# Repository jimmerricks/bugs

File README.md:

# Bugs

Opinionated ergonomic keyboards.

## Flea v0.1

## Gnat v0.2.1

## Midge v0.3

## Mosquito v0.1.1

## Wasp v0.1.1

## Yellowjacket v0.1.2

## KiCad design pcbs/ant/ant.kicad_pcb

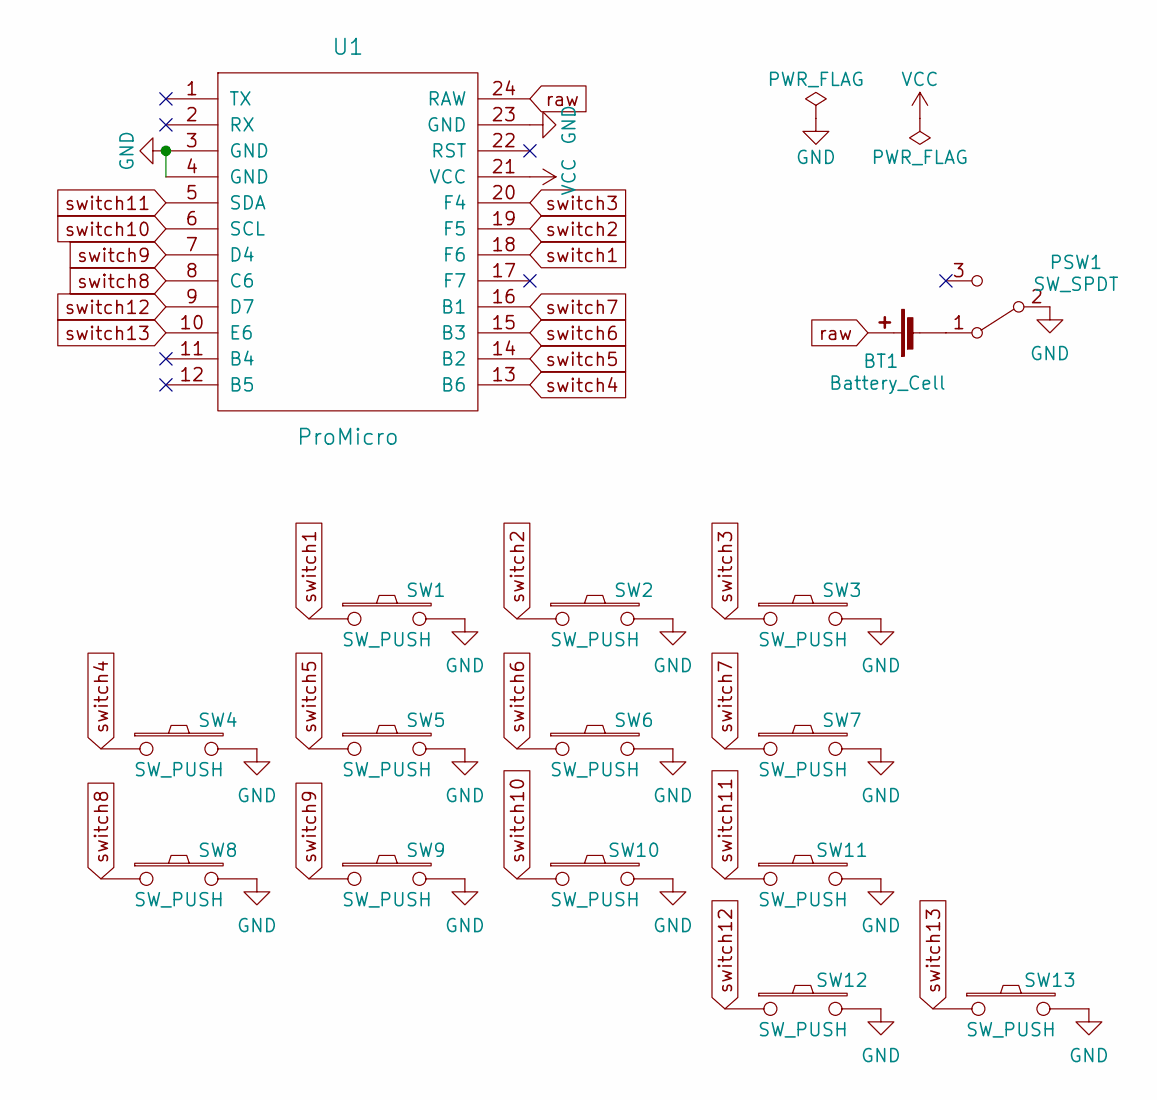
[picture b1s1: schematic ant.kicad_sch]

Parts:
BT1: Battery_Cell; Battery_pads_reversible
PSW1: SW_SPDT; Power_reversible
SW1, SW2, SW3, SW4, SW5, SW6, SW7, SW8, SW9, SW10, SW11, SW12, SW13: SW_PUSH; Choc_reversible
U1: ProMicro; ProMicro_jumpers

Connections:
GND: PSW1.2 (B), SW1.2, SW2.2, SW3.2, SW4.2, SW5.2, SW6.2, SW7.2, SW8.2, SW9.2, SW10.2, SW11.2, SW12.2, SW13.2, U1.3 (GND), U1.4 (GND), U1.23 (GND)
unnamed: BT1.2 (-), PSW1.1 (A)
VCC: U1.21 (VCC)
raw: BT1.1 (+), U1.24 (RAW)
switch1: SW1.1, U1.18 (F6)
switch2: SW2.1, U1.19 (F5)
switch3: SW3.1, U1.20 (F4)
switch4: SW4.1, U1.13 (B6)
switch5: SW5.1, U1.14 (B2)
switch6: SW6.1, U1.15 (B3)
switch7: SW7.1, U1.16 (B1)
switch8: SW8.1, U1.8 (C6)
switch9: SW9.1, U1.7 (D4)
switch10: SW10.1, U1.6 (SCL)
switch11: SW11.1, U1.5 (SDA)
switch12: SW12.1, U1.9 (D7)
switch13: SW13.1, U1.10 (E6)

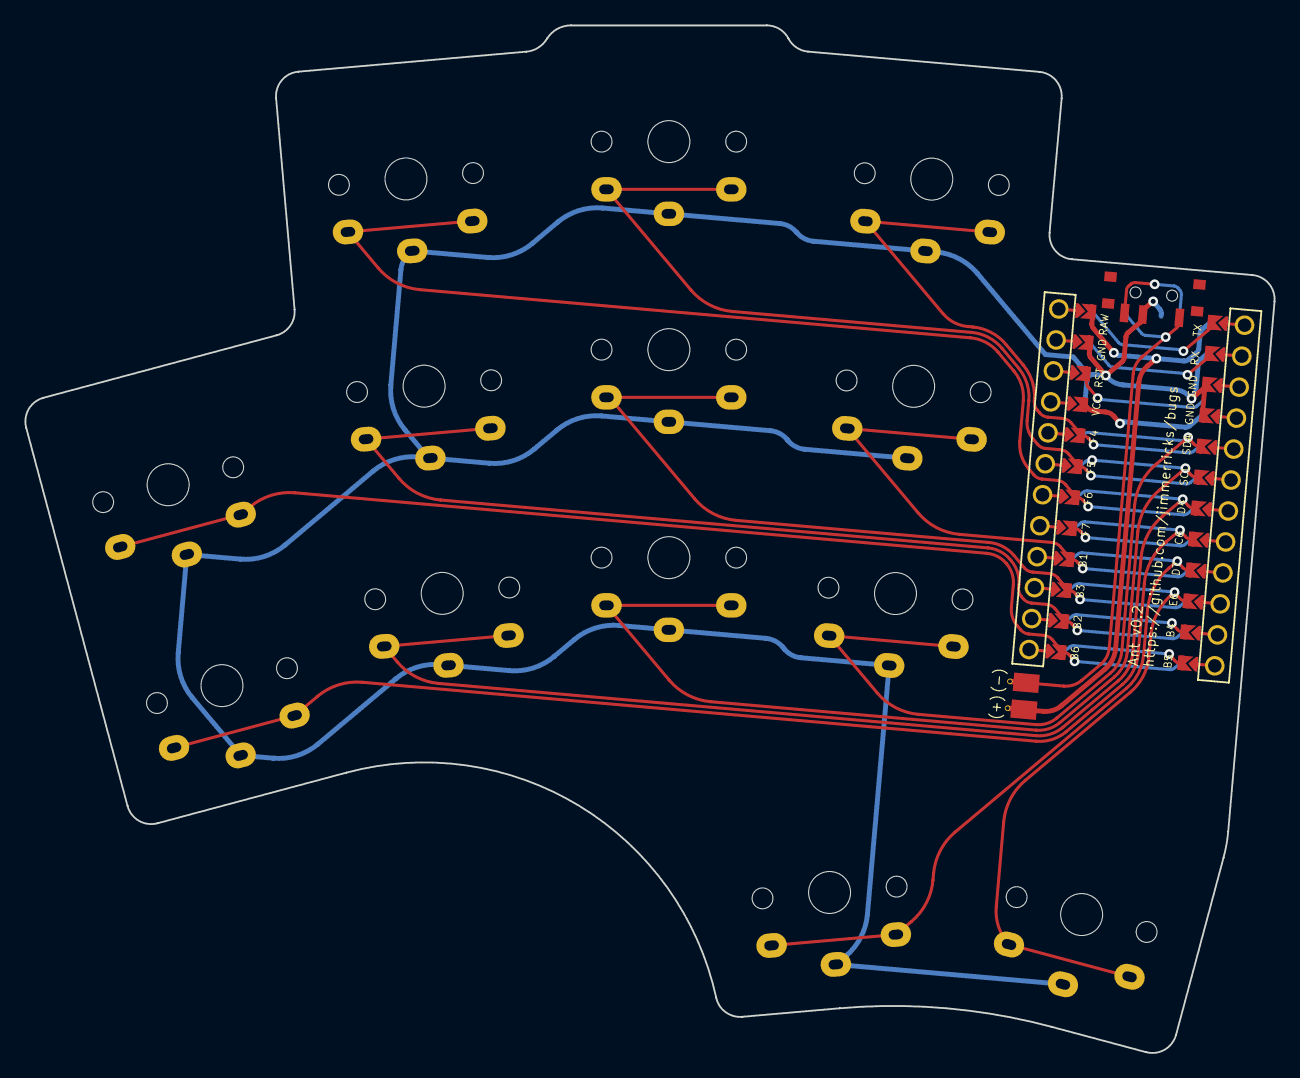
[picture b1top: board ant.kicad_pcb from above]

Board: 2 copper layers, 102.1 x 84.0 mm, 16 parts (0 on the bottom side), 16 nets.

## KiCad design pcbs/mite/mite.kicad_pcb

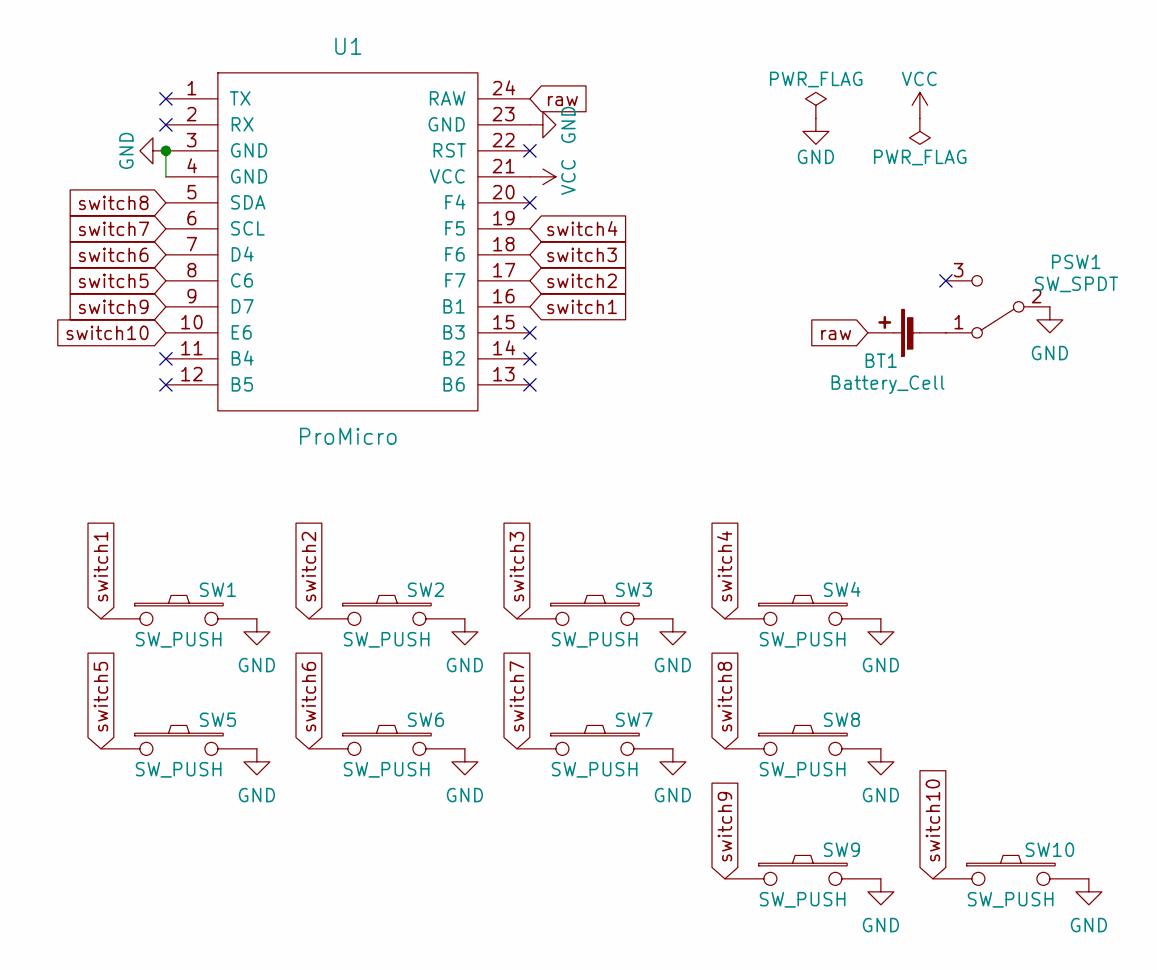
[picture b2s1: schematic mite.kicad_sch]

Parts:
BT1: Battery_Cell; Battery_pads_reversible
PSW1: SW_SPDT; Power_reversible
SW1, SW2, SW3, SW4, SW5, SW6, SW7, SW8, SW9, SW10: SW_PUSH; Choc_reversible
U1: ProMicro; ProMicro_jumpers

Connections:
GND: PSW1.2 (B), SW1.2, SW2.2, SW3.2, SW4.2, SW5.2, SW6.2, SW7.2, SW8.2, SW9.2, SW10.2, U1.3 (GND), U1.4 (GND), U1.23 (GND)
unnamed: BT1.2 (-), PSW1.1 (A)
VCC: U1.21 (VCC)
raw: BT1.1 (+), U1.24 (RAW)
switch1: SW1.1, U1.16 (B1)
switch2: SW2.1, U1.17 (F7)
switch3: SW3.1, U1.18 (F6)
switch4: SW4.1, U1.19 (F5)
switch5: SW5.1, U1.8 (C6)
switch6: SW6.1, U1.7 (D4)
switch7: SW7.1, U1.6 (SCL)
switch8: SW8.1, U1.5 (SDA)
switch9: SW9.1, U1.9 (D7)
switch10: SW10.1, U1.10 (E6)

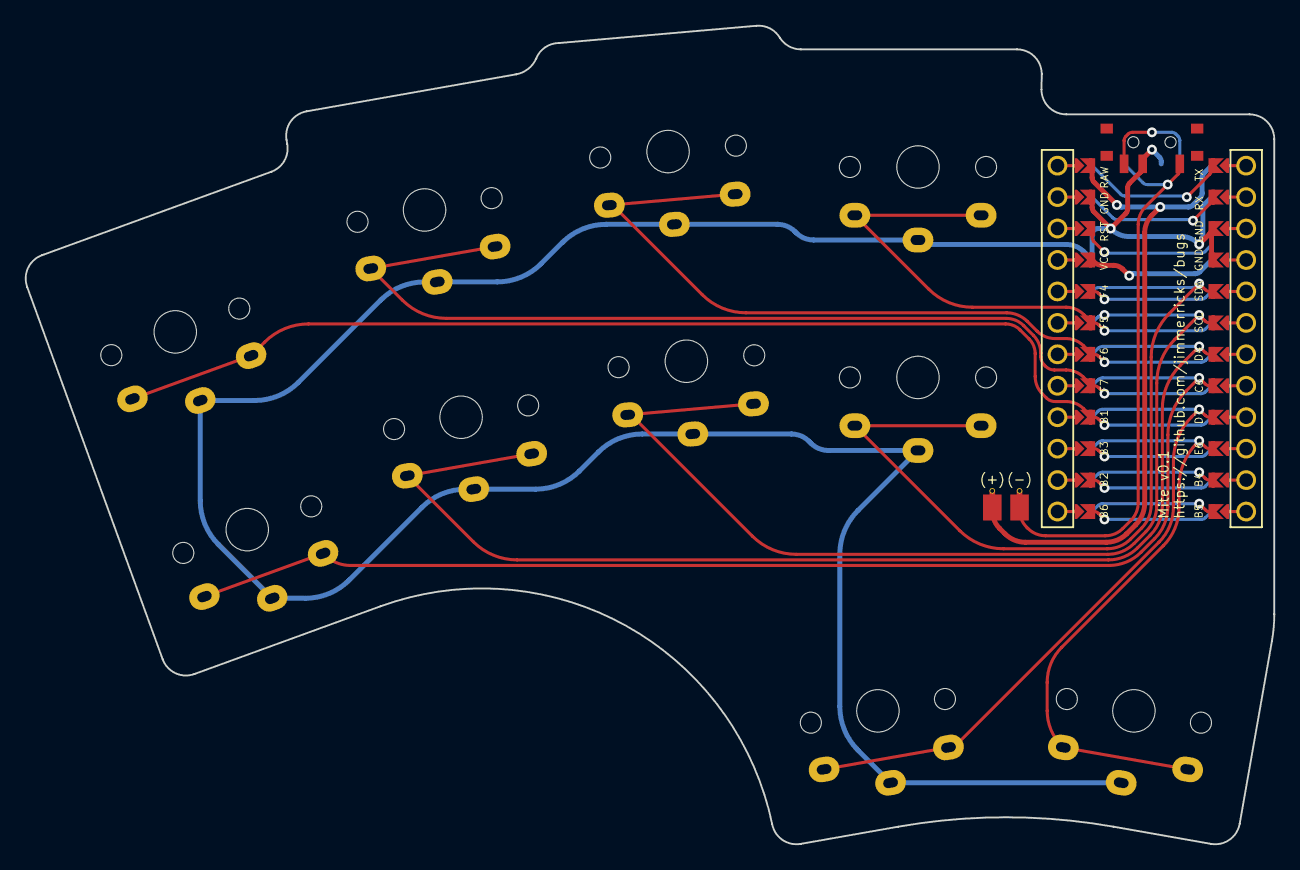
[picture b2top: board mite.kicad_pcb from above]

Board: 2 copper layers, 100.9 x 66.1 mm, 13 parts (0 on the bottom side), 13 nets.

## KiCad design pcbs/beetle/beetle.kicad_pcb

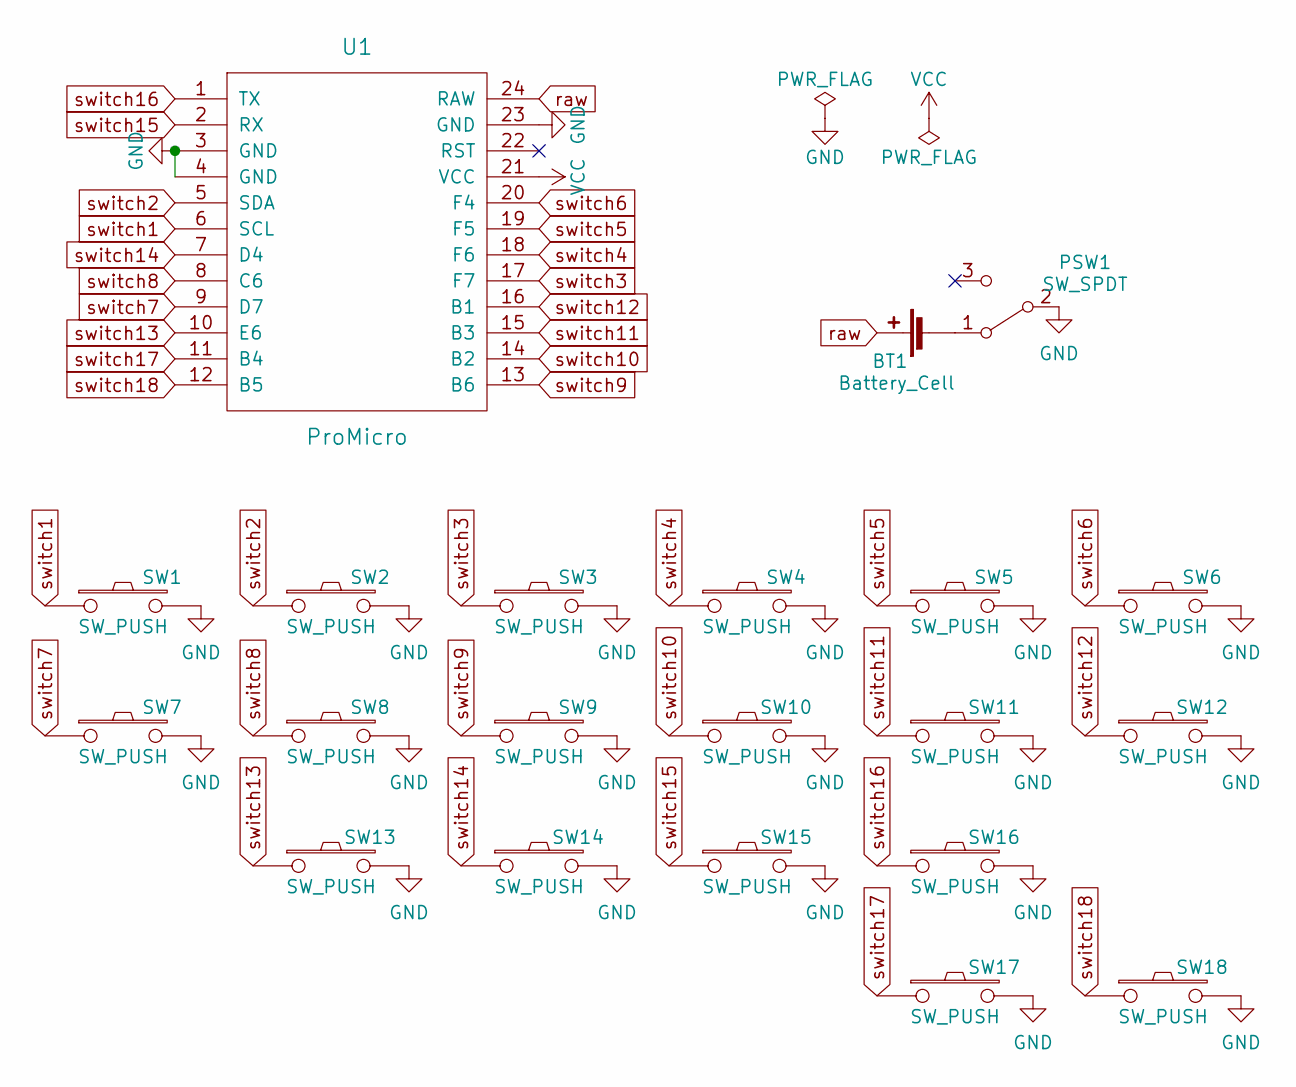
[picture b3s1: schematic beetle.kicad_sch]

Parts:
BT1: Battery_Cell; Battery_pads_reversible
PSW1: SW_SPDT; Power_reversible
SW1, SW2, SW3, SW4, SW5, SW6, SW7, SW8, SW9, SW10, SW11, SW12, SW13, SW14, SW15, SW16, SW17, SW18: SW_PUSH; Choc_reversible
U1: ProMicro; ProMicro_jumpers

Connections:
GND: PSW1.2 (B), SW1.2, SW2.2, SW3.2, SW4.2, SW5.2, SW6.2, SW7.2, SW8.2, SW9.2, SW10.2, SW11.2, SW12.2, SW13.2, SW14.2, SW15.2, SW16.2, SW17.2, SW18.2, U1.3 (GND), U1.4 (GND), U1.23 (GND)
unnamed: BT1.2 (-), PSW1.1 (A)
VCC: U1.21 (VCC)
raw: BT1.1 (+), U1.24 (RAW)
switch1: SW1.1, U1.6 (SCL)
switch2: SW2.1, U1.5 (SDA)
switch3: SW3.1, U1.17 (F7)
switch4: SW4.1, U1.18 (F6)
switch5: SW5.1, U1.19 (F5)
switch6: SW6.1, U1.20 (F4)
switch7: SW7.1, U1.9 (D7)
switch8: SW8.1, U1.8 (C6)
switch9: SW9.1, U1.13 (B6)
switch10: SW10.1, U1.14 (B2)
switch11: SW11.1, U1.15 (B3)
switch12: SW12.1, U1.16 (B1)
switch13: SW13.1, U1.10 (E6)
switch14: SW14.1, U1.7 (D4)
switch15: SW15.1, U1.2 (RX)
switch16: SW16.1, U1.1 (TX)
switch17: SW17.1, U1.11 (B4)
switch18: SW18.1, U1.12 (B5)

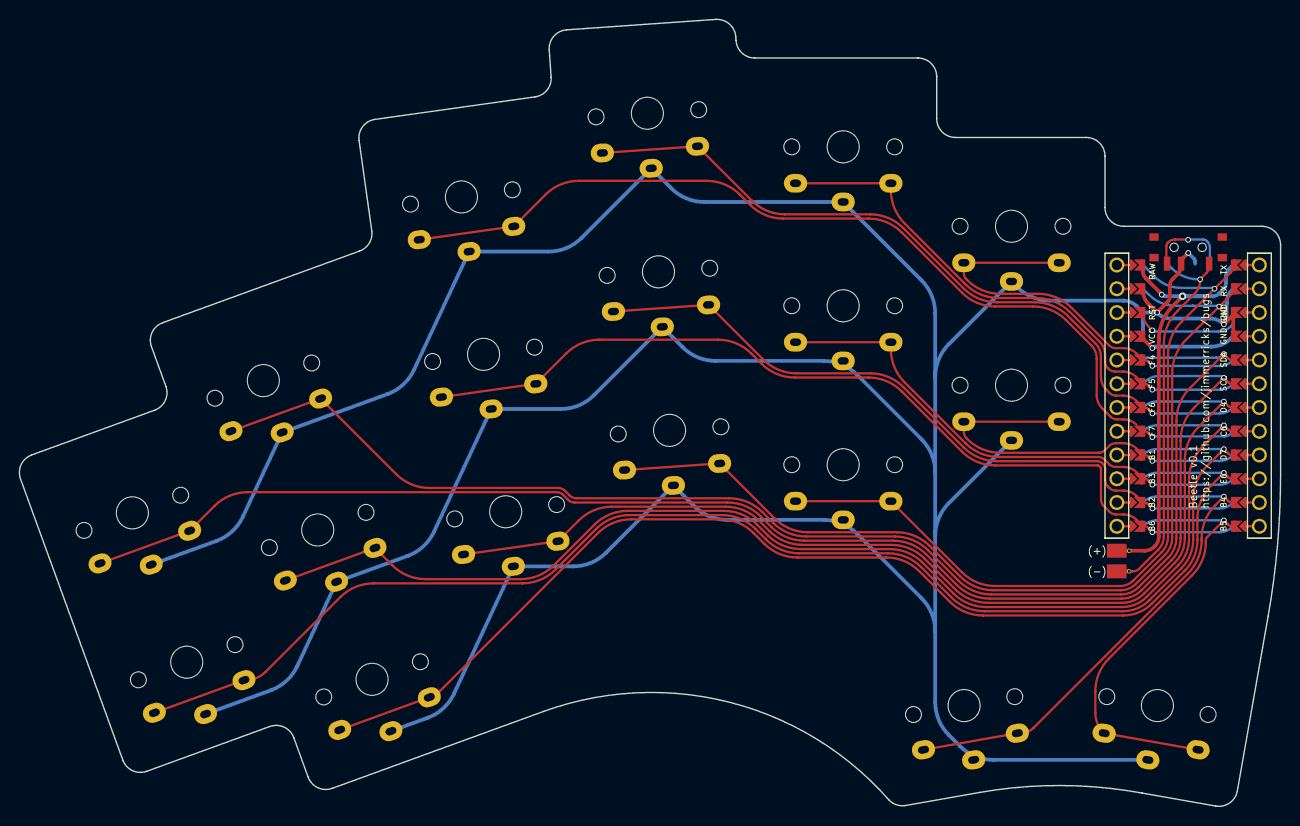
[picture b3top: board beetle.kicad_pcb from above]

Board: 2 copper layers, 134.9 x 84.2 mm, 21 parts (0 on the bottom side), 21 nets.

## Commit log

2021-09-17 v0.2, in preparation for open sourcing.
2021-09-17 Moved libraries into base directory.
2021-09-17 Moved gerbers into base directory.
2021-09-20 Renamed Knott to Midge.
2021-09-21 Added the Mosquito v0.1 files.
2021-10-04 Added the Cicada v0.1 files.
2021-10-07 Create LICENSE
2021-10-11 Added the Wasp 0.1 files.
2021-10-11 Renamed Cicada to Locust.
2021-10-11 First commit of Hornet keyboard.
2021-10-11 Fixed a couple of traces.
2021-10-27 Added a few images to the README.
2021-10-29 Updated the Midge to the jumper pro micro footprint, breaking the pin order.
2021-10-29 Renamed Locust to Termite and changed the battery footprint.
2021-10-29 Renamed Hornet to Yellowjacket.
2021-10-29 Tidied up and removed some defunct files.
2021-10-29 Added the Flea 0.1 files.
2021-10-31 Moved the pcbs into a subdirectory to tidy things up a little.
2021-10-31 Minor change and version bump for consistency with the Wasp.
2021-10-31 Added the Flea, Termite and Yellowjacket to the README.
2021-10-31 Fixed errors in the numbering.
2021-10-31 Not sure why the number didn't update on the jpg, but maybe this time.
2021-10-31 Third time's a charm.
2021-10-31 Modified the silkscreen on the Mosquito.
2021-12-22 Added the Beetle, a 36 key monster.
2021-12-22 A 20 key keyboard, what am I thinking?
2021-12-22 Minor edits
2022-01-01 The Ant is a 3x4+2 split.
2022-01-02 Renamed the Termite to the Gnat.
2022-01-02 Renamed the Termite to the Gnat in the docs.
2022-01-11 Dropped a key from the Ant.
